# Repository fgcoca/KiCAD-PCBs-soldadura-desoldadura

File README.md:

# MyKiCAD

En este repositorio iré publicando mis cosas sobre el software de diseño de PCBs KiCad

### **Presentaciones**

**Crear un proyecto con KiCad:**

La presentación siguiente se basa en el documento “Crear proyecto con KiCad” realizado por José García de abierto.cc, una plataforma para formadores donde compartir recursos educativos abiertos.

https://abierto.cc 

El documento original en pdf lo podemos encontrar en: https://abierto.cc/blog/post/5158/Empezando-a-disear-PCB/

A este documento se le pueden aportar sugerencias aquí:

https://docs.google.com/document/d/1d2NkisDbIFYeB7iv9PQkf9SkYmX3jAn-warP8IhUUpc/edit?usp=sharing

**Presentaciones**

[Archivo Fuente](https://github.com/fgcoca/MyKiCAD/blob/master/Presentaciones/Crear%20Proyecto/Archivos%20fuente/Crear%20proyecto%20con%20KiCad.odp)
[Archivo pdf](https://github.com/fgcoca/MyKiCAD/blob/master/Presentaciones/Crear%20Proyecto/pdfs/Crear%20proyecto%20con%20KiCad.pdf)

**Visualizar ficheros gerber en KiCad:**

[Archivo Fuente](https://github.com/fgcoca/MyKiCAD/blob/master/Presentaciones/Crear%20Proyecto/Archivos%20fuente/Visualizar%20gerber%20en%20KiCad.odp)
[Archivo pdf](https://github.com/fgcoca/MyKiCAD/blob/master/Presentaciones/Crear%20Proyecto/pdfs/Visualizar%20gerber%20en%20KiCad.pdf)

@ Placas de circuito impreso

Descripción básica de los distintos tipos de placas de circuito impreso para trabajar con circuitos electrónicos.

### **Author**

[Federico Coca Caba] (https://github.com/fgcoca)

### **License**
<br /> <a rel="license" href="http://creativecommons.org/licenses/by-sa/4.0/">Creative Commons Attribution-ShareAlike 4.0 International License</a>.

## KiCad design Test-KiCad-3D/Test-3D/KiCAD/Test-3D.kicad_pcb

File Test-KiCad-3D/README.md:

# Test-KiCad-3D

En esta entrada se puede encontrar toda la información necesaria para crear un modelo 3D en FreeCAD y llevarlo a KiCad para su visualización.

Están disponibles los archivos de diseño, los datasheet de donde se ha tomado la referencia y el archivo exportado listo para incluir en nuestras librerias de KiCad.

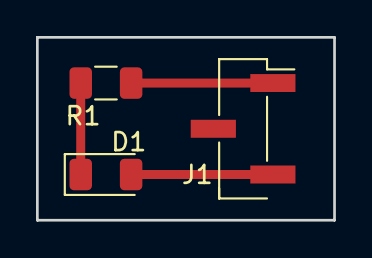
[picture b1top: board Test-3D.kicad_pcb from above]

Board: 2 copper layers, 16.5 x 10.2 mm, 3 parts (0 on the bottom side), 3 nets.

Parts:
D1: LED_ALT; LED_1206_3216Metric
J1: Screw_Terminal_01x03; PinHeader_1x03_P2.54mm_Vertical_SMD_Pin1Right
R1: 220; R_1206_3216Metric

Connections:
GND: J1.1, R1.1
unnamed: D1.1, R1.2
unnamed: D1.2, J1.3
